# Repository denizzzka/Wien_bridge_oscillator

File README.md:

### Wien bridge oscillator (Генератор с мостом Вина)

Details:
https://en.wikipedia.org/wiki/Wien_bridge_oscillator

This sine generator is made on the SMD-components with TL074C OpAmp and JFET used in the feedback regulator.

Repository contains:

* Qucs model
* KiCAD schematic and PCB design
* PCB routing created by TopoR

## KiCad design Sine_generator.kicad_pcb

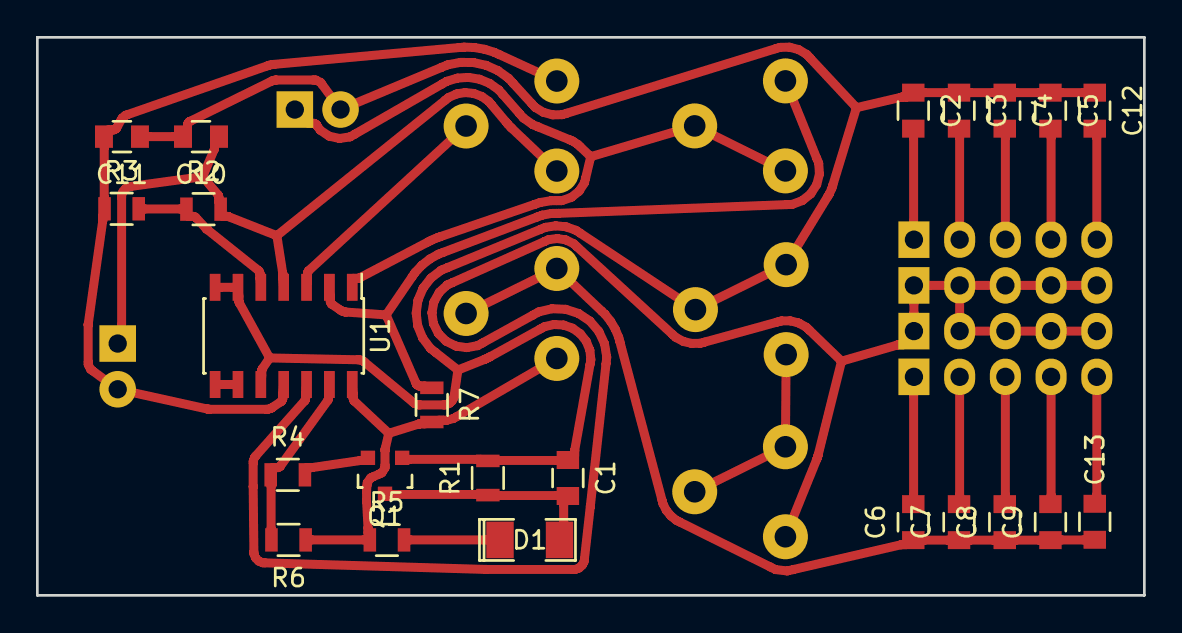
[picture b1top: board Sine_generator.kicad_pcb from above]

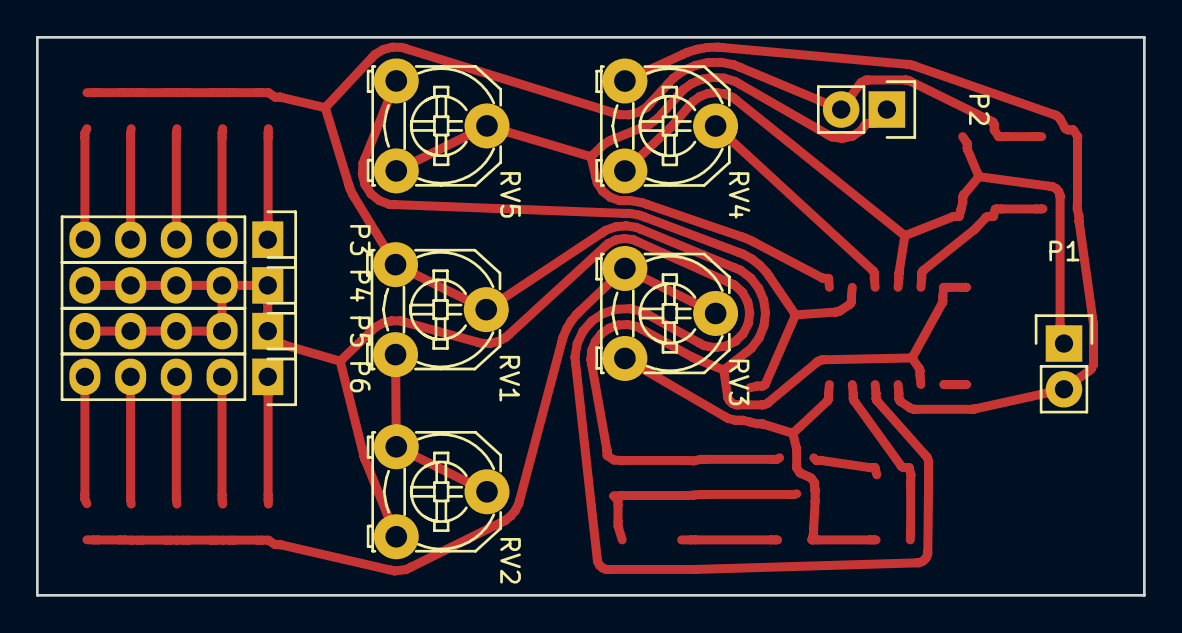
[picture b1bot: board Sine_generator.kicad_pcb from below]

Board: 2 copper layers, 61.5 x 31.0 mm, 34 parts (11 on the bottom side), 26 nets.

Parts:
C1, C2, C6: 1uF; C_0805
C3, C7: 100nF; C_0805
C4, C8: 10nF; C_0805
C5, C9: 1nF; C_0805
C10, C11: 2uF; C_0805
C12, C13: 100pF; C_0805
D1: 1N4148; SMD-1206_Pol
P1, P2: CONN_01X02; Pin_Header_Straight_1x02
P3, P4, P5, P6: CONN_01X05; Pin_Header_Straight_1x05
Q1: Q_NJFET_SDG; SOT-23
R1: 2M; R_0805
R2, R3: 100k; R_0805
R4: 2.7k; R_0805
R5: 200k; R_0805
R6: 10k; R_0805
R7: 1.5k; R_0805
RV1, RV3: 10k; Potentiometer_Triwood_RM-065
RV2: 500; Potentiometer_Triwood_RM-065
RV4: 200k; Potentiometer_Triwood_RM-065
RV5: 5k; Potentiometer_Triwood_RM-065
U1: TL074; SOIC-14_3.9x8.7mm_Pitch1.27mm

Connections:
GND: C1.1, C2.1, C3.1, C4.1, C5.1, C10.2, C11.1, C12.1, P2.2, Q1.1, R1.2, RV1.1, RV1.2, U1.6, U1.7, U1.10
unnamed: C1.2, D1.2, Q1.3, R1.1
unnamed: C2.2, P3.1
unnamed: C3.2, P3.2
unnamed: C4.2, P3.3
unnamed: C5.2, P3.4
unnamed: C6.2, P6.1
unnamed: C7.2, P6.2
unnamed: C8.2, P6.3
unnamed: C9.2, P6.4
unnamed: C12.2, P3.5
unnamed: C6.1, C7.1, C8.1, C9.1, C13.1, RV3.1, RV3.2
unnamed: C13.2, P6.5
unnamed: D1.1, R5.2
unnamed: P4.1, P4.2, P4.3, P4.4, P4.5, P5.1, P5.2, P5.3, P5.4, P5.5, RV2.3, U1.12
unnamed: Q1.2, R4.2
unnamed: R2.1, R3.2, U1.5
unnamed: R4.1, R6.2, U1.13
unnamed: R5.1, R6.1, R7.2, RV3.3, U1.14
unnamed: R7.1, RV5.1, U1.2
unnamed: RV1.3, RV2.1, RV2.2
unnamed: RV4.2, U1.3
unnamed: U1.8, U1.9
VCC: C10.1, P1.1, R2.2, RV4.3, U1.4
VEE: C11.2, P1.2, R3.1, RV4.1, U1.11
signal: P2.1, RV5.2, RV5.3, U1.1

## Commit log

2016-05-02 initial
2016-05-02 readme fix
2016-05-02 readme
2016-05-02 decrease images size
2016-05-03 IC name fix
